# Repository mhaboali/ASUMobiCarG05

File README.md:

# ASUMobiCarG05
It is required to develop a Mobile Controlled Car. The car allow easy driving with obstacles avoidance, accurate movement, line tracking. 

Phases videos:

https://www.youtube.com/watch?v=lcx6RJcDALI

https://www.youtube.com/watch?v=eNSwdOZkeOM

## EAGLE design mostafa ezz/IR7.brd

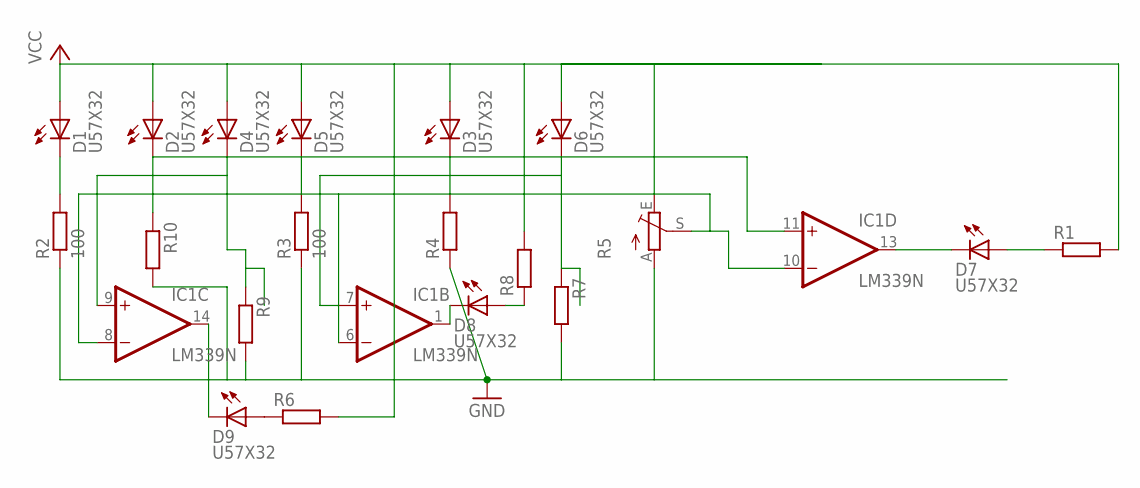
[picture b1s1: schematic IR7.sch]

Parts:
D1, D2, D3, D4, D5, D6, D7, D8, D9: U57X32
IC1: LM339N; DIL14
R1, R4, R6, R7, R8, R9, R10: R-EU_0204/7; 0204/7
R2, R3: 100; 0204/7
R5: TRIM_1234-S64YW; S64YW

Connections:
GND: IC1.12 (GND), R2.1, R3.1, R4.1, R5.A, R7.2, R9.2, R10.2
unnamed: D1.K (C), R2.2
unnamed: D5.K (C), R3.2
unnamed: D3.K (C), R4.2
unnamed: D8.A, R8.1
unnamed: D9.A, R6.1
unnamed: D7.K (C), IC1.13 (OUT)
unnamed: D7.A, R1.1
unnamed: IC1.6 (-IN), IC1.8 (-IN), IC1.10 (-IN), R5.S
unnamed: D6.K (C), IC1.7 (+IN), R7.1
unnamed: D4.K (C), IC1.9 (+IN), R9.1
unnamed: D2.K (C), IC1.11 (+IN), R10.1
unnamed: D9.K (C), IC1.14 (OUT)
unnamed: D8.K (C), IC1.1 (OUT)
VCC: D1.A, D2.A, D3.A, D4.A, D5.A, D6.A, IC1.3 (V+), R1.2, R5.E, R6.2, R8.2

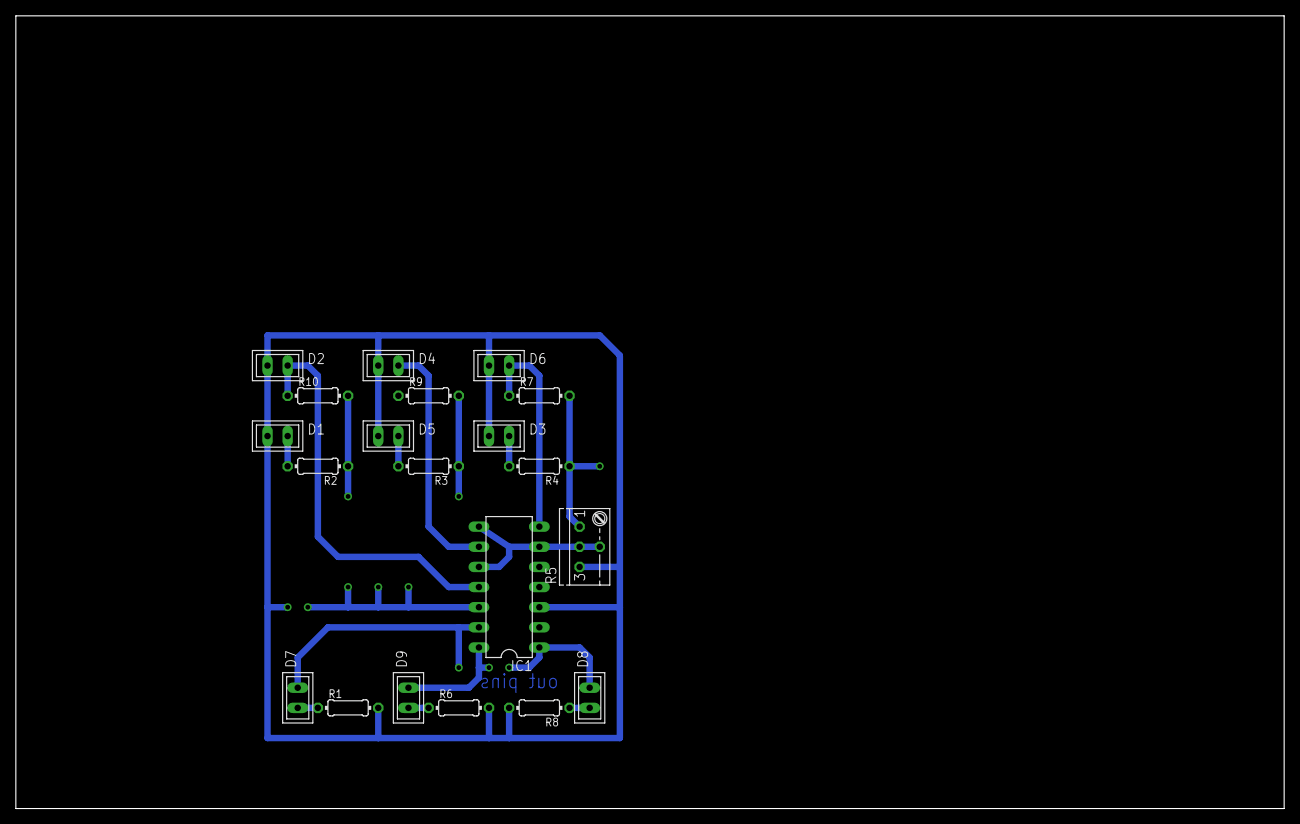
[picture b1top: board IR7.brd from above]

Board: 2 copper layers, 160.0 x 100.0 mm, 20 parts (0 on the bottom side), 15 nets.

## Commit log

2018-02-13 Commit Folders Of Members
2018-02-14 just test
2018-02-14 test
2018-02-14 test1
2018-02-14 test2
2018-02-15 Rename 1.txt to 1
2018-02-15 Rename 1 to solve many of car's problems
2018-02-15 Rename solve many of car's problems to solutions
2018-02-15 Update solutions
2018-02-16 first
2018-02-16 adding a new file
2018-02-16 doc 1
2018-02-16 features2
2018-02-16 Sensors
2018-02-16 Ideas Search
2018-02-16 Second Week
2018-02-16 Add files via upload
    sensors and car design
2018-02-19 Start Arduino Code
2018-02-19 Sheet 1 - Q(1)
    Write embedded program that produces continuous pulses with duration of 2 seconds and duty cycle of 25%.
2018-02-19 Sheet 1 -Q(2)
    Write embedded program that show a bouncing light between 4 LEDs connected to pins 4, 5, 6 and 7. The bouncing delay is 1 second.
    Explanation: Bouncing light means that the light is moving between the LEDs in turn. At first it starts form left to right then go back from right to left and so on.
2018-02-19 Sheet 1 -Q2
    Write embedded program that show a bouncing light between 4 LEDs connected to pins 4, 5, 6 and 7. The bouncing delay is 1 second.
    Explanation: Bouncing light means that the light is moving between the LEDs in turn. At first it starts form left to right then go back from right to left and so on.
2018-02-19 Sheet 1 -Q(1)
    Write embedded program that produces continuous pulses with duration of 2 seconds and duty cycle of 25%.
2018-02-21 Update Easy Driving
2018-02-24 Create avoiding
2018-02-25 Create update avoiding
2018-02-27 IR sensor
    IR sensor
2018-03-03 Update to the servo Code
    Updating the initial position for the servo so it can rotate left and right by 30 degrees
2018-03-03 Testing Servo Code on Online Simulator
    Small Video Testing Servo code using TinkerCad
2018-03-04 steering mechanism 3d design assembly added
2018-03-05 final code
2018-03-06 new cost added
2018-03-06 Add files via upload
    working code on easy driving mode
2018-03-10 Batteries for Phase 1 Vid
2018-03-10 Placing Servo Simulation in Proper File
2018-03-10 Final Code For Phase 1 with Comments
2018-03-25 Embedded C
2018-03-29 Embedded C V2
2018-03-30 Create How H-Brige IC is internally designed ?
2018-03-30 How H-Bridge IC is internally designed ?
2018-03-31 Embedded C V3
2018-04-03 Speed Sensor Code 1
    Measuring speed using encoder and photointerrupter speed sensor with interrupt in code
2018-04-03 Websites Resources
    This File will include some websites that I used to figure out the code and the algorithms
2018-04-03 Optimizing Code Trial 1
2018-04-04 Trial to optimize code 1
2018-04-07 Create first_trial_line_follower_using_4_IR__without_PID
2018-04-08 Embedded C Phase1 without testing
2018-04-09 Add files via upload
    line follower design
2018-04-14 adding println on speed sensor code
2018-06-17 Create line follower competition with PID
2018-06-25 control0
2018-06-25 control1
2018-06-25 control2
2018-07-03 Phase 3 speed sensor trial 3
2018-07-05 Rectangle Trial
2018-07-05 Phase 3 Code
